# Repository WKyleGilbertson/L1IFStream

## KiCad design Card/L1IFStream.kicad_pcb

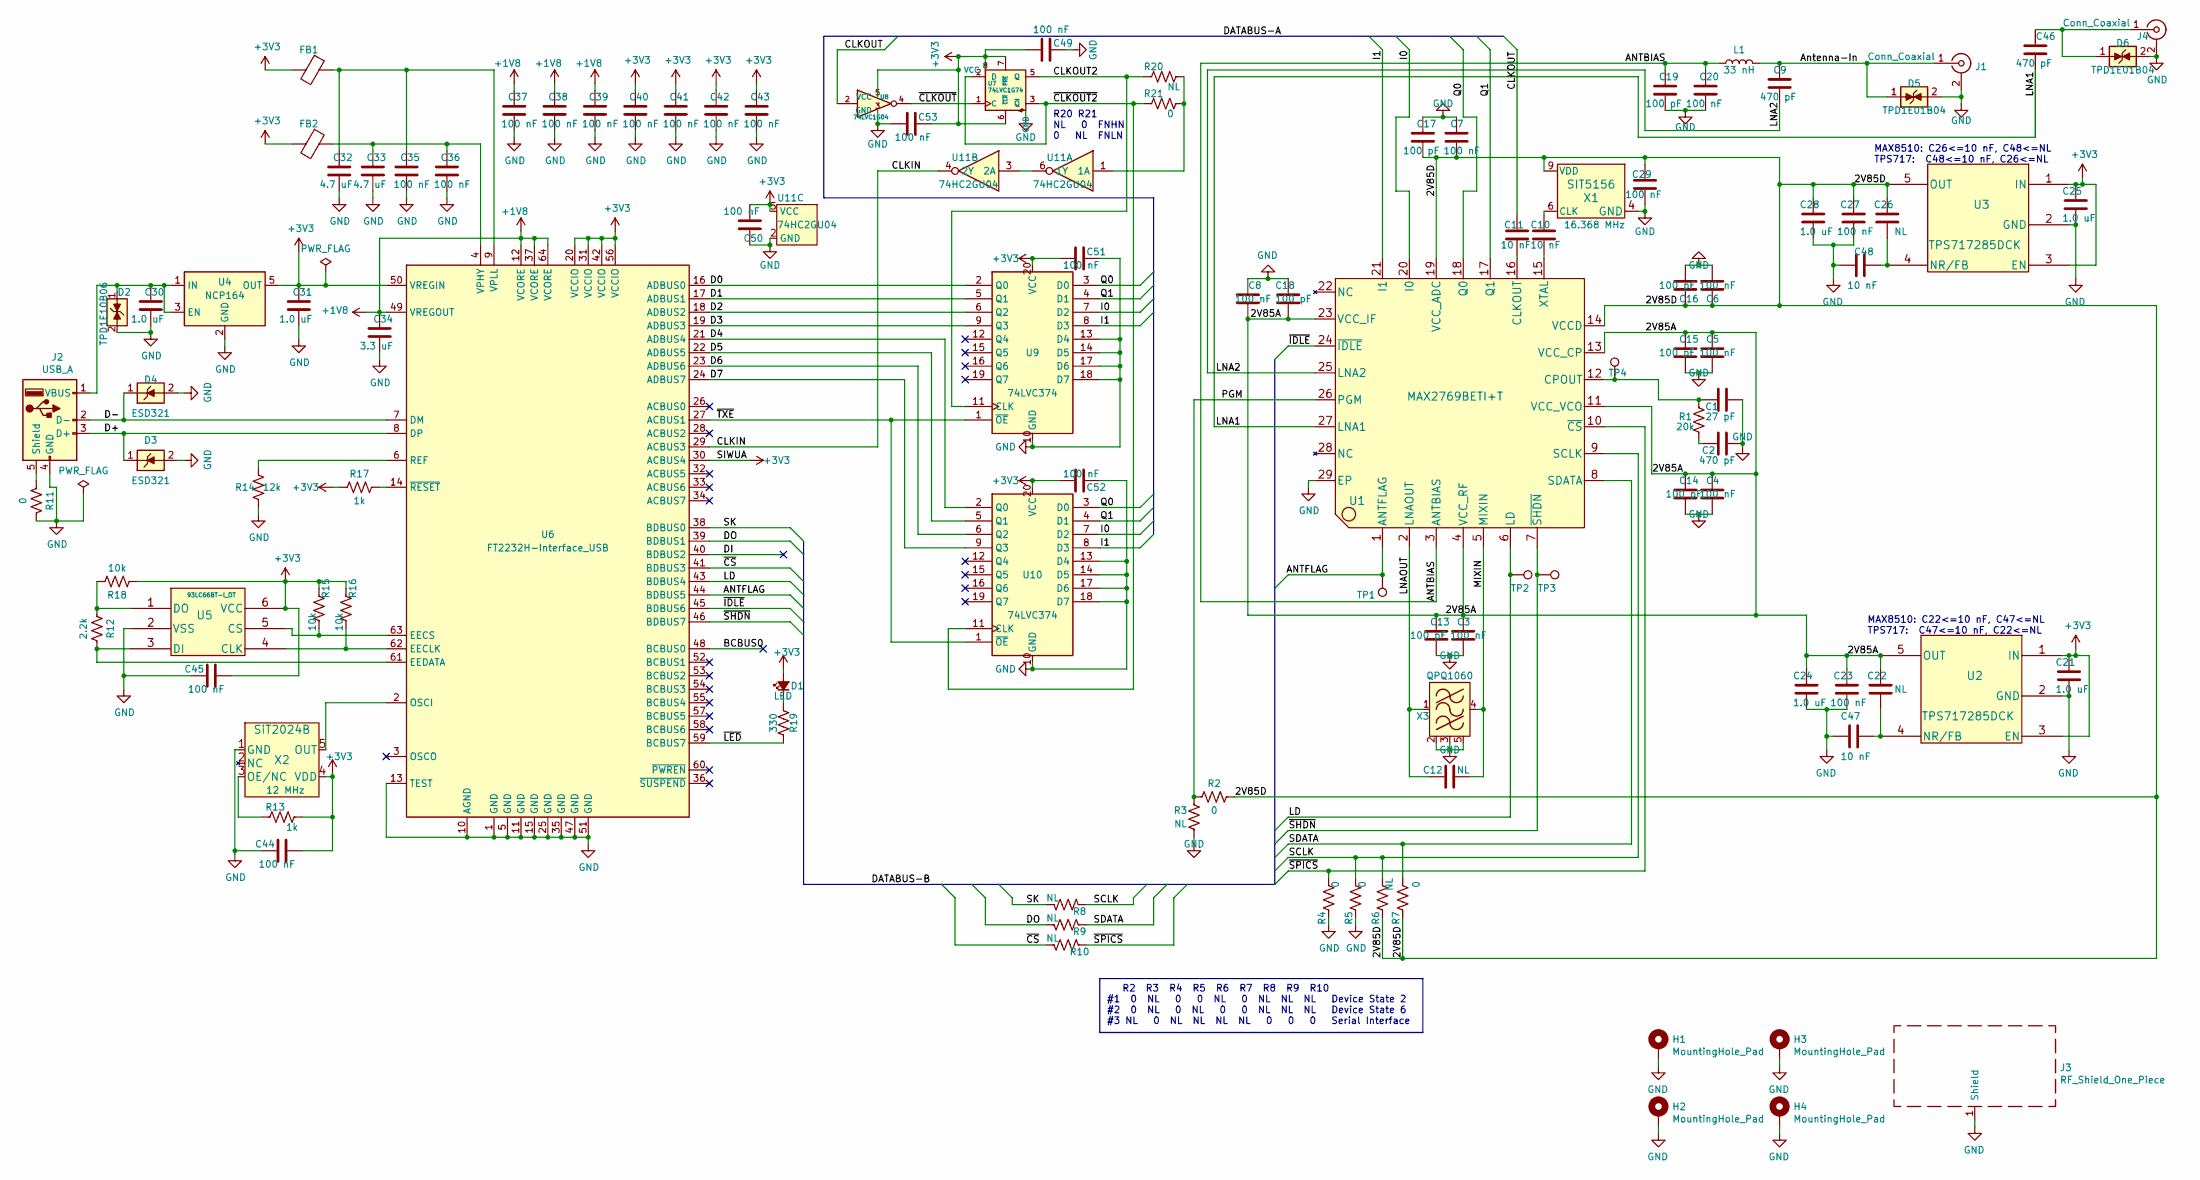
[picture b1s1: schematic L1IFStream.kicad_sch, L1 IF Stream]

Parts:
C1: 27 pF; C_0402_1005Metric; MPN GCM1555C1H270JA16D
C2, C9, C46: 470 pF; C_0402_1005Metric; MPN GRM1555C1H471JA01J
C3, C4, C5, C6, C7, C8, C20, C23, C27, C29, C35, C36, C37, C38, C39, C40, C41, C42, C43, C44, C45, C49, C50, C51, C52, C53: 100 nF; C_0402_1005Metric; MPN GRM155R71C104KA88J
C10, C11, C47, C48: 10 nF; C_0402_1005Metric; MPN C0402C103K8RAC7867
C12: NL; C_0402_1005Metric; MPN GRM1555C1H471JA01J
C13, C14, C15, C16, C17, C18, C19: 100 pF; C_0402_1005Metric; MPN C0402C101J5GAC7867
C21, C24, C25, C28, C30, C31: 1.0 uF; C_0402_1005Metric; MPN GRT155C80J105KE01D
C22, C26: NL; C_0402_1005Metric; MPN C0402C103K8RAC7867
C32, C33: 4.7 uF; C_0805_2012Metric; MPN C0805C475J9RACAUTO
C34: 3.3 uF; C_0805_2012Metric; MPN GCM21BR71C335KA73L
D1: LED; LED_0603_1608Metric; MPN QBLP601-AG1-2943
D2: TPD1E10B06; Texas_DPY0002A_0.6x1mm_P0.65mm; MPN TPD1E10B06QDPYRQ1
D3, D4: ESD321; Texas_DPY0002A_0.6x1mm_P0.65mm; MPN ESD321DPYR
D5, D6: TPD1E01B04; Texas_DPY0002A_0.6x1mm_P0.65mm; MPN TPD1E01B04DPYRQ1
FB1, FB2: Ferrite_Bead; C_0805_2012Metric; MPN BLM21AG102SN1D
H1, H2, H3, H4: MountingHole_Pad; MountingHole_2.2mm_M2_Pad_Via
J1: Conn_Coaxial; SMA_Amphenol_132203-12_Horizontal; MPN 132136
J2: USB_A; USB_A_CNCTech_1001-011-01101_Horizontal; MPN 0480372200
J3: RF_Shield_One_Piece; Laird_Technologies_BMI-S-103_26.21x26.21mm; MPN BMI-S-103
J4: Conn_Coaxial; MMCX_Molex_73415-1471_Vertical; MPN 908-22106
L1: 33 nH; L_0402_1005Metric; MPN LQG15HS33NJ02D
R1: 20k; R_0603_1608Metric; MPN RK73H1JTTD2002F
R2, R4, R5, R7, R11, R21: 0; R_0603_1608Metric; MPN RK73Z1JTTD
R3, R6, R8, R9, R10, R20: NL; R_0603_1608Metric; MPN RK73Z1JTTD
R12: 2.2k; R_0603_1608Metric; MPN RK73H1JTTD2201F
R13, R17: 1k; R_0603_1608Metric; MPN RK73H1JTTD1001F
R14: 12k; R_0603_1608Metric; MPN RK73H1JTTD1202F
R15, R16, R18: 10k; R_0603_1608Metric; MPN RK73H1JTTD1002F
R19: 330; R_0603_1608Metric; MPN RK73H1JTTD3300F
TP1, TP2, TP3, TP4: TestPoint; TestPoint_Pad_D1.0mm
U1: MAX2769BETI+T; QFN-28_EP_5.63x5.63_Pitch0.5mm; MPN MAX2769BETI/V+
U2, U3: TPS717285DCK; MPN TPS717285DCK
U4: NCP164; TSOP-5; MPN NCP164CSN330T1G
U5: 93LC66BT-I_OT; SOT-23-6; MPN 93LC66BT-I/OT
U6: FT2232H-Interface_USB; LQFP-64_10x10mm_P0.5mm; MPN FT2232HL-REEL
U7: 74LVC1G74; SOT-833-1; MPN 74LVC1G74GT,115
U8: 74LVC1G04; SOT-353_SC-70-5; MPN 74LVC1G04GW,125
U9, U10: 74LVC374; TSSOP-20_4.4x6.5mm_P0.65mm; MPN 74LVC374APW,118
U11: 74HC2GU04; SOT-363_SC-70-6; MPN 74HC2GU04GW,125
X1: SIT5156; 10L_CQFN; MPN SIT5156AICFK-30N0-16.368000
X2: SiT2024B; SOT-23-5; MPN SIT2024BA-S8-33E-12.000000
X3: QPQ1060; QPQ1060_1.4x1.2; MPN QPQ1060SR

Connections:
+1V8: C34.1, C37.1, C38.1, C39.1, U6.12 (VCORE), U6.37 (VCORE), U6.49 (VREGOUT), U6.64 (VCORE)
+3V3: C21.1, C25.1, C31.1, C40.1, C41.1, C42.1, C43.1, C44.2, C45.2, C49.2, C50.2, C51.1, C52.1, C53.2, D1.2 (A), FB1.2, FB2.2, R13.1, R15.2, R16.2, R17.2, R18.2, U2.1 (IN), U2.3 (EN), U3.1 (IN), U3.3 (EN), U4.5 (OUT), U5.6 (VCC), U6.20 (VCCIO), U6.30 (ACBUS4), U6.31 (VCCIO), U6.42 (VCCIO), U6.50 (VREGIN), U6.56 (VCCIO), U7.6 (~CLR), U7.7 (~PRE), U7.8 (VCC), U8.5 (VCC), U9.20 (VCC), U10.20 (VCC), U11.5 (VCC), X2.4 (VDD)
/2V85A: C3.1, C4.1, C5.1, C8.2, C13.1, C14.1, C15.1, C18.2, C22.1, C23.1, C24.1, U1.4 (VCC_RF), U1.11 (VCC_VCO), U1.13 (VCC_CP), U1.23 (VCC_IF), U2.5 (OUT)
/2V85D: C6.1, C7.2, C16.1, C17.2, C26.1, C27.1, C28.1, C29.1, R2.1, R6.2, R7.2, U1.14 (VCCD), U1.19 (VCC_ADC), U3.5 (OUT), X1.9 (VDD)
/ANTBIAS: C19.1, C20.1, L1.1, U1.3 (ANTBIAS)
/ANTFLAG: TP1.1 (1_1), U1.1 (ANTFLAG), U6.44 (BDBUS5)
/Antenna-In: C9.1, D5.1 (K), J1.1 (In), L1.2
/BCBUS0: U6.48 (BCBUS0)
/CLKIN: U6.29 (ACBUS3), U11.4 (2Y)
/CLKOUT: C11.1, U8.2
/CLKOUT2: R20.2, U7.5 (Q), U9.11 (CLK)
/D0: U6.16 (ADBUS0), U9.2 (Q0)
/D1: U6.17 (ADBUS1), U9.5 (Q1)
/D2: U6.18 (ADBUS2), U9.6 (Q2)
/D3: U6.19 (ADBUS3), U9.9 (Q3)
/D4: U6.21 (ADBUS4), U10.2 (Q0)
/D5: U6.22 (ADBUS5), U10.5 (Q1)
/D6: U6.23 (ADBUS6), U10.6 (Q2)
/D7: U6.24 (ADBUS7), U10.9 (Q3)
/D+: D3.1 (K), J2.3 (D+), U6.8 (DP)
/D-: D4.1 (K), J2.2 (D-), U6.7 (DM)
/DI: U6.40 (BDBUS2)
/DO: R9.2, U6.39 (BDBUS1)
/I0: U1.20 (I0), U9.7 (D2), U10.7 (D2)
/I1: U1.21 (I1), U9.8 (D3), U10.8 (D3)
/LD: TP2.1 (1_1), U1.6 (LD), U6.43 (BDBUS4)
/LNA1: C46.2, U1.27 (LNA1)
/LNA2: C9.2, U1.25 (LNA2)
/LNAOUT: C12.1, U1.2 (LNAOUT), X3.1 (IN)
/MIXIN: C12.2, U1.5 (MIXIN), X3.4 (OUT)
/PGM: R2.2, R3.2, U1.26 (PGM)
/Q0: U1.18 (Q0), U9.3 (D0), U10.3 (D0)
/Q1: U1.17 (Q1), U9.4 (D1), U10.4 (D1)
/SCLK: R5.2, R6.1, R8.1, U1.9 (SCLK)
/SDATA: R7.1, R9.1, U1.8 (SDATA)
/SK: R8.2, U6.38 (BDBUS0)
/~CLKOUT2: R21.2, U7.2 (D), U7.3 (~Q), U10.11 (CLK)
/~CLKOUT: U7.1 (C), U8.4
/~CS: R10.2, U6.41 (BDBUS3)
/~IDLE: U1.24 (~IDLE), U6.45 (BDBUS6)
/~LED: R19.2, U6.59 (BCBUS7)
/~SHDN: TP3.1 (1_1), U1.7 (~SHDN), U6.46 (BDBUS7)
/~SPICS: R4.2, R10.1, U1.10 (~CS)
/~TXE: U6.27 (ACBUS1), U9.1 (~OE), U10.1 (~OE)
GND: C1.2, C2.2, C3.2, C4.2, C5.2, C6.2, C7.1, C8.1, C13.2, C14.2, C15.2, C16.2, C17.1, C18.1, C19.2, C20.2, C21.2, C23.2, C24.2, C25.2, C27.2, C28.2, C29.2, C30.2, C31.2, C32.2, C33.2, C34.2, C35.2, C36.2, C37.2, C38.2, C39.2, C40.2, C41.2, C42.2, C43.2, C44.1, C45.1, C47.2, C48.2, C49.1, C50.1, C51.2, C52.2, C53.1, D2.2 (A), D3.2 (A), D4.2 (A), D5.2 (A), D6.2 (A), H1.1 (1_1), H2.1 (1_1), H3.1 (1_1), H4.1 (1_1), J1.2 (Ext), J2.4 (GND), J3.1 (Shield_1), J4.2 (Ext), R3.1, R4.1, R5.1, R11.2, R14.2, U1.29 (EP), U2.2 (GND), U3.2 (GND), U4.2 (GND), U5.2 (VSS), U6.1 (GND), U6.5 (GND), U6.10 (AGND), U6.11 (GND), U6.13 (TEST), U6.15 (GND), U6.25 (GND), U6.35 (GND), U6.47 (GND), U6.51 (GND), U7.4 (GND), U8.3 (GND), U9.10 (GND), U9.13 (D4), U9.14 (D5), U9.17 (D6), U9.18 (D7), U10.10 (GND), U10.13 (D4), U10.14 (D5), U10.17 (D6), U10.18 (D7), U11.2 (GND), X1.4 (GND), X2.1 (GND), X3.2 (GND), X3.3 (GND), X3.5 (GND)
unnamed: C2.1, R1.2
unnamed: D1.1 (K), R19.1
unnamed: C30.1, D2.1 (K), J2.1 (VBUS), U4.1 (IN), U4.3 (EN)
unnamed: C46.1, D6.1 (K), J4.1 (In)
unnamed: J2.5 (Shield), R11.1
unnamed: C11.2, U1.16 (CLKOUT)
unnamed: C1.1, R1.1, TP4.1 (1_1), U1.12 (CPOUT)
unnamed: C10.2, U1.15 (XTAL)
unnamed: C22.2, C47.1, U2.4 (NR/FB)
unnamed: C26.2, C48.1, U3.4 (NR/FB)
unnamed: R16.1, U5.4 (CLK), U6.62 (EECLK)
unnamed: R15.1, U5.5 (CS), U6.63 (EECS)
unnamed: R12.1, U5.3 (DI), U6.61 (EEDATA)
unnamed: R12.2, R18.1, U5.1 (DO)
unnamed: U6.2 (OSCI), X2.5 (OUT)
unnamed: R14.1, U6.6 (REF)
unnamed: C33.1, C36.1, FB2.1, U6.4 (VPHY)
unnamed: C32.1, C35.1, FB1.1, U6.9 (VPLL)
unnamed: R17.1, U6.14 (~RESET)
unnamed: R20.1, R21.1, U11.1 (1A)
unnamed: U11.3 (2A), U11.6 (1Y)
unnamed: C10.1, X1.6 (CLK)
unnamed: R13.2, X2.3 (OE/NC)

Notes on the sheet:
MAX8510: C26<=10 nF, C48<=NL TPS717: C48<=10 nF, C26<=NL
R2 R3 R4 R5 R6 R7 R8 R9 R10 #1 0 NL 0 0 NL 0 NL NL NL Device State 2 #2 0 NL 0 NL 0 0 NL NL NL Device State 6 #3 NL 0 NL NL NL NL 0 0 0 Serial Interface
MAX8510: C22<=10 nF, C47<=NL TPS717: C47<=10 nF, C22<=NL
R20 R21 NL 0 FNHN 0 NL FNLN

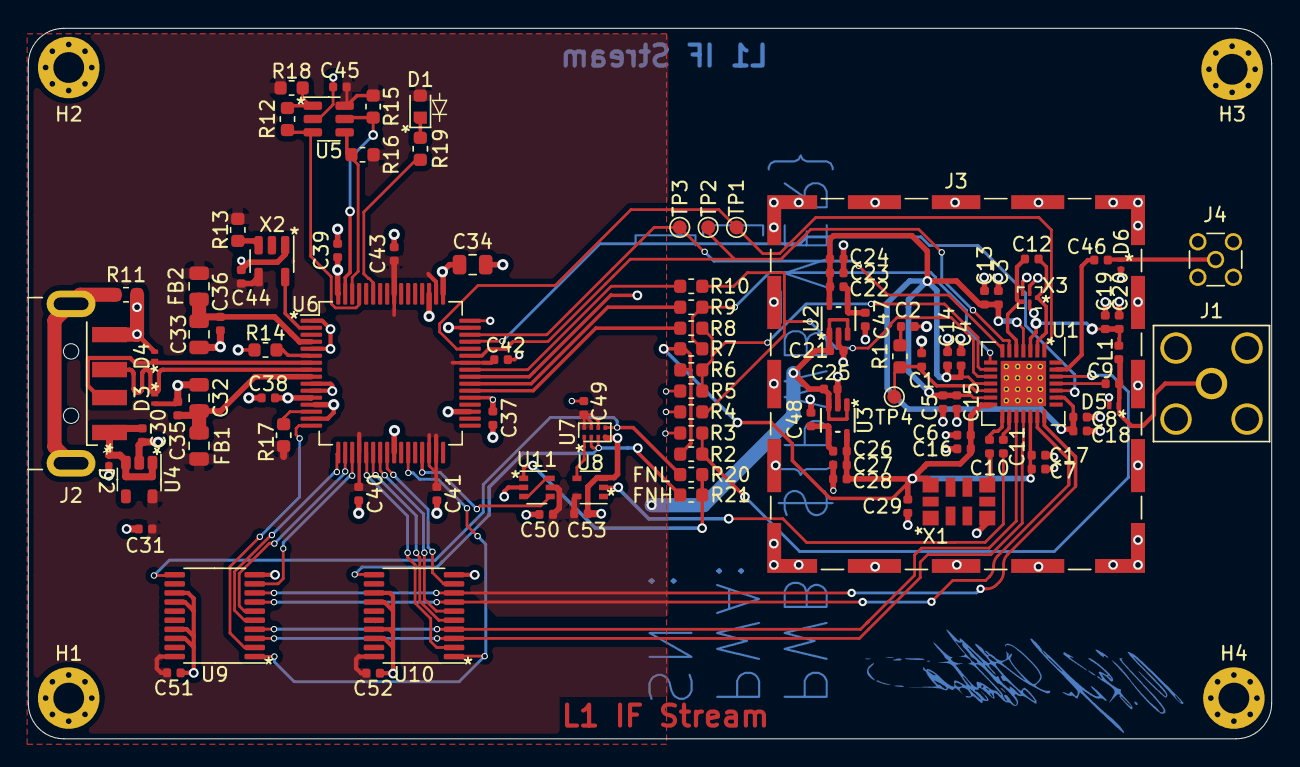
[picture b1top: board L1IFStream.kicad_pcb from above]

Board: 4 copper layers, 88.9 x 50.8 mm, 110 parts (0 on the bottom side), 66 nets.

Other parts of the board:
QR*****: NAVSTARGPS.US

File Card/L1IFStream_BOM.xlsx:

Component Count: |  | 107
Collated Components:
Item | Description | Qty | Reference(s) | Value | Manufacturer | MPN | Vendor | Vendor P/N# | Notes
1 | CAP CER 27PF 50V C0G/NP0 0402 5% | 1 | C1 | 27 pF | Murata | GCM1555C1H270JA16D | DigiKey | 490-12651-1-ND
2 | CAP CER 470PF 50V C0G/NP0 0402 10% | 3 | C2, C9, C46 | 470 pF | Murata | GRM1555C1H471JA01J | DigiKey | 490-6242-1-ND
3 | CAP CER 0.1UF 16V X7R 0402 10% | 26 | C3, C4, C5, C6, C7, C8, C20, C23, C27, C29, C35, C36, C37, C38, C39, C40, C41, 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 | 100 nF | Murata | GRM155R71C104KA88J | DigiKey | 490-6328-1-ND
4 | CAP CER 10000PF 10V X7R 0402 10% | 4 | C10, C11, C47, C48 | 10 nF | Kemet | C0402C103K8RAC7867 | DigiKey | 399-7759-1-ND
5 | CAP CER 470PF 50V C0G/NP0 0402 10% | 3 | C12, C22, C26 | NL | DNP | DNP | DNP | DNP | DNP
6 | CAP CER 100PF 50V C0G/NP0 0402 5% | 7 | C13, C14, C15, C16, C17, C18, C19 | 100 pF | Kemet | C0402C101J5GAC7867 | DigiKey | 399-3194-1-ND
7 | CAP CER 1UF 6.3V X6S 0402 | 6 | C21, C24, C25, C28, C30, C31 | 1.0 uF | Murata | GRT155C80J105KE01D | DigiKey | 490-12233-1-ND
8 | CAP CER 4.7UF 6.3V X7R 0805 | 2 | C32, C33 | 4.7 uF | Kemet | C0805C475J9RACAUTO | DigiKey | 399-15725-1-ND
9 | CAP CER 3.3UF 16V X7R 0805 | 1 | C34 | 3.3 uF | Murata | GCM21BR71C335KA73L | DigiKey | 490-13309-1-ND
10 |  | 1 | D1 | LED | QTBrightek (QTB) | QBLP601-AG1-2943 | DigiKey | QBLP601-AG1-2943
11 | TVS DIODE 5.5VWM 14VC 2X1SON | 1 | D2 | TPD1E10B06 | Texas Instruments | TPD1E10B06QDPYRQ1 | DigiKey | 296-TPD1E10B06QDPYRQ1DKR-ND
12 | TVS DIODE 3.6VWM 6.8VC 2X1SON | 2 | D3, D4 | ESD321 | Texas Instruments | ESD321DPYR | DigiKey | 296-51108-6-ND
13 | AUTOMOTIVE 0.18-PF, 3.6-V, 15-KV | 2 | D5, D6 | TPD1E01B04 | Texas Instruments | TPD1E01B04DPYRQ1 | DigiKey | 296-TPD1E01B04DPYRQ1DKR-ND
14 | FERRITE BEAD 1 KOHM 0805 1LN | 2 | FB1, FB2 | Ferrite_Bead | Murata | BLM21AG102SN1D | DigiKey | 490-1041-1-ND
15 |  | 4 | H1, H2, H3, H4 | MountingHole_Pad | PCB MFR |  | MFR
16 | CONN SMA JACK R/A 50 OHM PCB | 1 | J1 | Conn_Coaxial | Amphenol RF | 132136 | DigiKey | ACX1232-ND
17 | CONN PLUG USB2.0 TYPEA 4P SMD RA | 1 | J2 | USB_A | Molex | 480372200 | DigiKey | WM3983CT-ND
18 | RF SHIELD 1.032"X1.032" SLDR 1PC | 1 | J3 | RF_Shield_One_Piece | Laird Technologies EMI | BMI-S-103 | DigiKey | 903-1008-1-ND
19 | CONN MMCX JACK STR 50 OHM PCB | 1 | J4 | Conn_Coaxial | Amphenol RF | 908-22106 | DigiKey | ARF1904-ND
20 | FIXED IND 33NH 350MA 580 MOHM | 1 | L1 | 33 nH | Murata | LQG15HS33NJ02D | DigiKey | 490-2629-1-ND
21 | RES 20K OHM 1% 1/10W 0603 | 1 | R1 | 20k | KOA Speer Electronics, Inc. | RK73H1JTTD2002F | DigiKey | 2019-RK73H1JTTD2002FCT-ND
22 | RES 0 OHM JUMPER 0603 | 5 | R2, R4, R5, R7, R11 | 0 | KOA Speer Electronics, Inc. | RK73Z1JTTD | DigiKey | 2019-RK73Z1JTTDCT-ND
23 | RES 0 OHM JUMPER 0603 | 5 | R3, R6, R8, R9, R10 | NL | DNP | DNP | DNP | DNP | DNP
24 | RES 2.2K OHM 1% 1/10W 0603 | 1 | R12 | 2.2k | KOA Speer Electronics, Inc. | RK73H1JTTD2201F | DigiKey | 2019-RK73H1JTTD2201FCT-ND
25 | RES 1K OHM 1% 1/8W 0603 | 1 | R13 | 1k | KOA Speer Electronics, Inc. | RK73H1JTTD1001F | DigiKey | 2019-RK73H1JTTD1001FCT-ND
26 | RES 12K OHM 1% 1/10W 0603 | 1 | R14 | 12k | KOA Speer Electronics, Inc. | RK73H1JTTD1202F | DigiKey | 2019-RK73H1JTTD1202FCT-ND
27 | RES 10K OHM 1% 1/10W 0603 | 3 | R15, R16, R18 | 10k | KOA Speer Electronics, Inc. | RK73H1JTTD1002F | DigiKey | 2019-RK73H1JTTD1002FCT-ND
28 | RES 1K OHM 1% 1/8W 0603 | 1 | R17 | 1k | KOA Speer Electronics, Inc. | RK73H1JTTD1001F | DigiKey | 2019-RK73H1JTTD1001FCT-ND
29 | RES 330 OHM 1% 1/8W 0603 | 1 | R19 | 330 | KOA Speer Electronics, Inc. | RK73H1JTTD3300F | DigiKey | 2019-RK73H1JTTD3300FDKR-ND
30 |  | 4 | TP1, TP2, TP3, TP4 | TestPoint | PCB MFR |  | MFR
31 | RF RX GNSS 1575.42MHZ 28TQFN | 1 | U1 | MAX2769ETI+T | Analog Devices Inc./ Maxim Integrated | MAX2769BETI/V+ | DigiKey | 175-MAX2769BETI/V+-ND
32 | IC REG LINEAR 2.85V 150MA SC70-5 | 2 | U2, U3 | TPS717285DCKR | Texas Instruments | TPS717285DCKR | DigiKey | 296-19649-1-ND
33 | LDO 300 MA AD 3.3V, ULTRA | 1 | U4 | NCP164CSN330T1G | Onsemi | NCP164CSN330T1G | DigiKey | 488-NCP164CSN330T1GCT-ND
34 | IC EEPROM 4K SPI 2MHZ SOT23-6 | 1 | U5 | 93LC66BT-I_OT | Microchip | 93LC66BT-I/OT | DigiKey | 93LC66BT-I/OTCT-ND
35 | IC USB HS DUAL UART/FIFO 64-LQFP | 1 | U6 | FT2232H-Interface_USB | FTDI | FT2232HL-REEL | DigiKey | 768-1024-1-ND
36 | IC FF D-TYPE SNGL 1BIT 8XSON | 1 | U7 | 74LVC1G74 | Nexperia | 74LVC1G74GT,115 | DigiKey | 1727-3558-1-ND
37 | IC INVERTER 1CH 1-INP 5TSSOP | 1 | U8 | 74LVC1G04 | Nexperia | 74LVC1G04GW,125 | DigiKey | 1727-2871-1-ND
38 | IC FF D-TYPE SNGL 8BIT 20TSSOP | 2 | U9, U10 | 74LVC374 | Nexperia | 74LVC374APW,118 | DigiKey | 1727-4034-1-ND
39 | IC INVERTER 2CH 2-INP 6TSSOP | 1 | U11 | 74HC2GU04 | Nexperia | 74HC2GU04GW,125 | DigiKey | 1727-6915-6-ND
40 | MEMS OSC TCXO 16.3680MHZ | 1 | X1 | SIT5156 | SiTime | SIT5156AICFK-30N0-16.368000 | DigiKey | 1473-SIT5156AICFK-30N0-16.368000-ND
41 | MEMS OSC XO 12.0000MHZ LVCMOS LV | 1 | X2 | SIT2024BA-S8-33E-12.00000E | SiTime | SIT2024BA-S8-33E-12.000000 | DigiKey | 1473-SIT2024BA-S8-33E-12.000000G-ND
42 | Signal Conditioning L1 TC-SAW, GSO | 1 | X3 | QPQ1060 | Qorvo | QPQ1060SR | Mouser | 772-QPQ1060SR
Source: |  | C:\git\GPS\L1IFStream\Card\L1IFStream.kicad_sch
Date: |  | 45119.450462962966
Tool: |  | Eeschema 7.0.6
Generator: |  | C:\Programs\KiCad\7.0\bin\scripting\plugins/bom_csv_grouped_by_value.py

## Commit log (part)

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2023-06-19 First commit of L1 IF Stream Board
2023-06-19 Added Circuit protection diodes
2023-06-21 Added PMOD connector
2023-06-21 Added SPI lines to PMOD connector
2023-06-21 Added Tallysman Antenna Mount
2023-06-29 Added Thumb Drive Outline
2023-06-29 Potential Board Layout
2023-07-07 Clean up
2023-07-10 Added SMA and USB 3D model
2023-07-10 Added STEP files
2023-07-10 Flip Clocks to Reorder Nibbles
2023-07-10 Prepare to make new card
2023-07-11 Cleaned up Qorvo footprint
2023-07-11 Verifying Footprints -- Qorvo and SiTime Checked, TVS needs minor tweaks
2023-07-12 All new parts identified on schematic. Need minor adjustments in layout.
2023-07-12 Ready for prototype quote
2023-07-12 Added Pick and Place File
2023-07-12 Floof planning USB stick
2023-07-12 Start looking for smaller parts
2023-07-13 Adding SAW filter to footprints
2023-07-13 Some floor planning
2023-07-13 Added 3D model of QPQ1060SR
2023-07-14 Broke out MPN
2023-07-14 Sent to 4PCB.com
2023-07-14 Changed symbol properties for cleaner BOM generation
2023-07-14 U11 should be unbuffered inverter. Should it be non-inverting?
2023-07-14 Need to rework the symbol library
2023-07-18 Added STEP files for some parts
2023-07-18 Added shield STEP file
2023-07-20 Changed solder mask minimum web width to 0.05 mm
2023-07-24 Sent parts to PCBway
2023-07-24 Rotated schematic -- updated some footprints to use local library
2023-07-25 Reoriented schematic
2023-08-01 Midway through prototype run at PCBWay
2023-08-01 Added ability to choose nibble order with zero ohm resistors
2023-08-03 BDBUS2 is input only. Moved LED to BCBUS0.
2023-08-04 Initial commit of Antenna status checker
2023-08-05 Reworked bad command check into its own function
2023-08-05 More function consolidation
2023-08-06 collected GPIO byte read into its own function
2023-08-07 Broke out status bit values
2023-08-07 First Pass Status Complete
2023-08-07 Attempt to add context through Makefile
2023-08-07 First attempt at Shutdown and Idle
2023-08-08 GPIO Complete Status
2023-08-08 Clean state until SPI addition
2023-08-09 Reworked send and receive pieces into respective data structures
2023-08-09 More cleanup
2023-08-09 Completed conversiont to tx/rx data structs
2023-08-09 Added SPI config and stuff to set GPS Clock rate, but haven't tested it.
2023-08-10 Changed Sample Speed, but SPI CS enable part does not look right
2023-08-10 Removed SPI sample rate adjustment
2023-08-10 Some cleanup on L1IFStat. Changed some visibility on layout
2023-08-10 Decoding the SPI bus interface
2023-08-11 Still mirky on the SPI direction mask, but it seems to be working
2023-08-11 Rearranged a bit. Not sure about configureSPI relating to the 0x80 OpCode
2023-08-11 Moved SPI programming stuff around
2023-08-11 Files sent to PCBWay to test boards
2023-08-11 Not sure what changed here other than setting visibility of layers
2023-08-15 Moved L1IFStat to its own repo
2023-10-02 Packing slip for second round of parts
2023-10-20 Got L1IFStat to run on pilot run from PCBWAY
2023-10-20 Continues to pass L1IFStat
2023-10-20 Renamed flash template to avoid conflict with BOM intermediary file
2023-10-20 Changed serial number prefix to two characters, L1
2023-10-20 The first five cards Serial Numbers
2023-10-21 Fixed LED Circuit
2023-10-21 Added test points to attach SPI device
2023-10-24 Debating how much to fix. Current Argument, just the LED circuit
2023-10-26 Need to cleanup library for Macrofab compatibility
2023-11-01 Squared up L1IFTHMB and L1IFStream to implement the same nibble selector
2023-11-07 Started cleaning up symbol library
2023-11-09 Library clean up of oscillators and U1
2023-11-09 Cleaned up library through U3
2023-11-09 Library clean up through U4
2023-11-09 Updated U4 to Library part
2023-11-13 Library cleaned up except for Rs and Cs
2023-11-13 Library cleanup capacitors
2023-11-13 Capacitor silk placement
2023-11-14 Library cleaned up through resistors. Just caps to go.
2023-11-14 Library Cleaned Up
2023-11-14 Seemingly ready to make more
2023-11-14 Should only need L1IF symbol and footprints now.
2023-11-16 Added SiTime 5156 16.367667 oscillator as alternate.
2023-11-16 Cleaned up some routes and separated grounds.
2023-12-04 Changed License to CERN-OHL-W v2
2024-02-13 Added standoff dimensions and moved fiducial targets
2024-02-13 Minor drawing cleanup with more needed
2024-02-13 Revert "Files sent to PCBWay to test boards"
    This reverts commit 74a9a0324716ddeedc07c467053088ec7fdbbe32.
2024-06-21 Removed Creative Commons and replaced with CERN
2026-05-04 Attempt to use dual LVC flip-flops. Doesn't appear to save any space
2026-05-04 Rearranged bit order

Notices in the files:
Card/L1IFStream.kicad_pcb:
https://cern.ch/cern-ohl
License: CERN-OHL-W-2.0
